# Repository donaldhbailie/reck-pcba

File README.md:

# reck-pcba
The Resourceful Embedded Circuity Kit Printed Circuit Board Assembly (RECK PCBA) is a custom board talored to teach new Peer Instructors (PIs) all of the basic and advanced embedded use cases seen in the HIVE Makerspace.

Integrates a microcontroller, probe-able SPI, I2C, UART, motor drivers, servo drivers, power electronics, and commonly used sensors.

### Basic Embedded:
- ESP32-S3 (Microcontroller Hardware/Software Control Flow)
- Pushbuttons (Digital Input)
- Single LEDs (Digital Output)
- Photoresistor (Analog Input)
- Potentiometer (Analog Input)
- Analog-to-Digital Converter (Internal ADC; Read Analog Signals)
- Magnetic Buzzer (Audio Ouput)
- Voltage Translation (Level Shifting)
  
### Advanced Embedded:
- IMU (SPI Interface)
- Barometric Pressure and Humidity Sensor (SPI Interface)
- IR Ranging Sensor (I2C Interface)
- Digital-to-Analog Converter (I2C Interface; Output Analog Signals)
- Servos (PWM Interface)
- DC Brushed Motors (PWM Interface)
- Chained LEDs (PWM Interface)

## Schematic Preview

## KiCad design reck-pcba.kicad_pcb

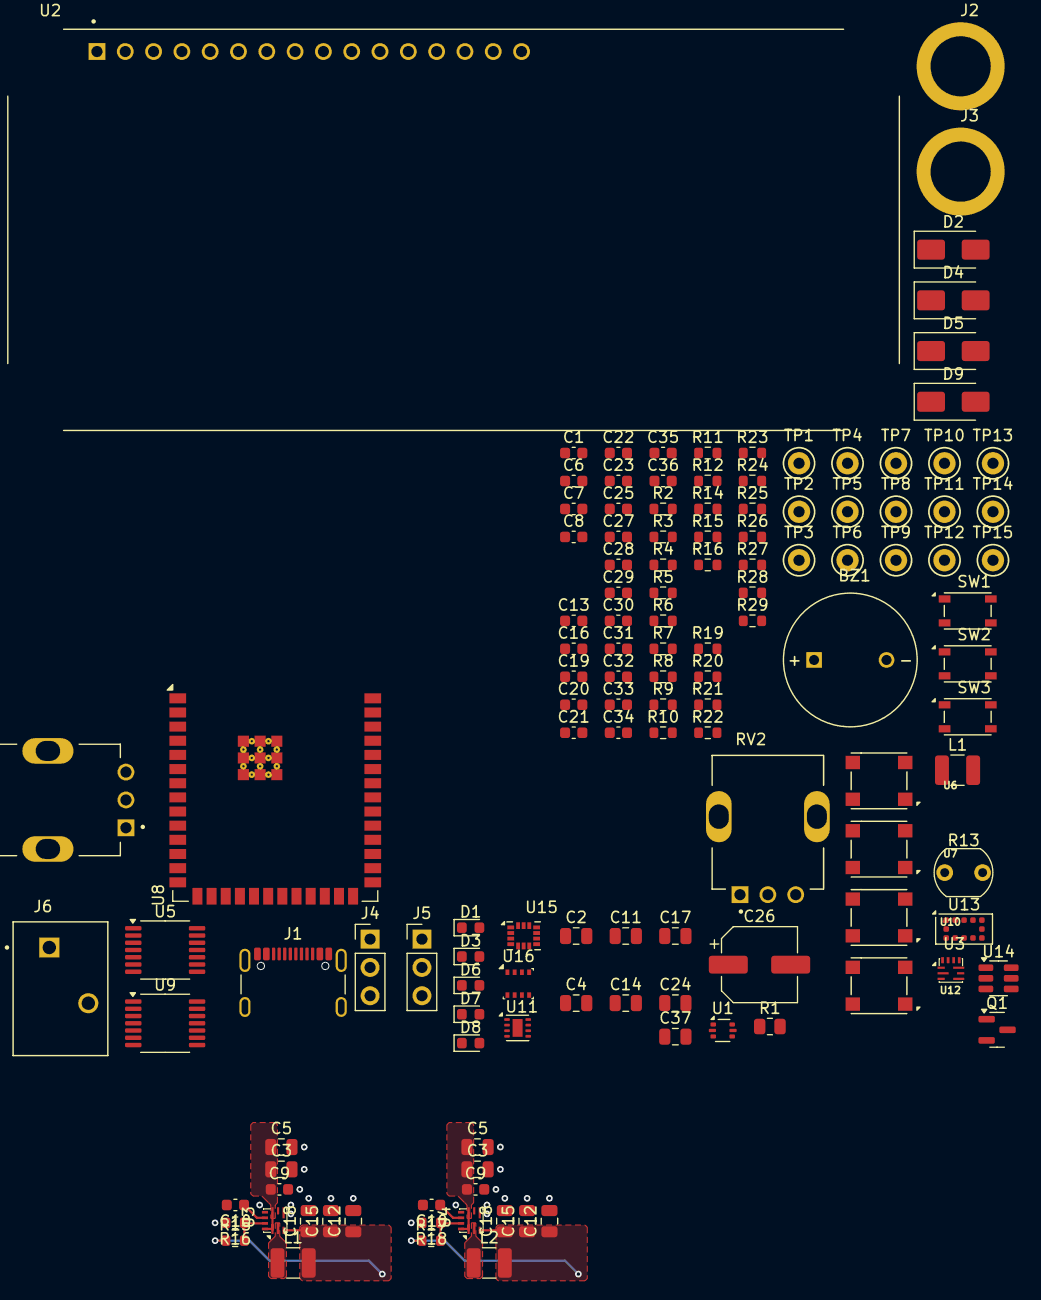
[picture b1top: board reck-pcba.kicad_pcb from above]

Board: 4 copper layers, 132 parts (0 on the bottom side), 75 nets.

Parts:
BZ1: CEM-1206S
C1, C7, C9, C9#2: 2.2nF; C_0603_1608Metric
C2, C3, C3#2, C4, C5, C5#2, C37: 10uF; C_0805_2012Metric
C6, C8, C10, C10#2: 1uF; C_0603_1608Metric
C11, C12, C12#2, C14, C15, C15#2, C17, C18, C18#2, C24: 22uF; C_0805_2012Metric
C13, C16, C19, C20, C21, C22, C23, C25, C27, C28, C29, C30, C31, C32, C33, C34, C35, C36: 100nF; C_0603_1608Metric
C26: 47uF; CP_Elec_6.3x5.9
D1, D3, D6, D7, D8: LED; LED_0603_1608Metric
D2, D4, D9: CDBA340L-HF; D_SMA
D5: 1SMA5928BT3G; D_SMA
J1: USB4105-GF-A; USB_C_Receptacle_GCT_USB4105-xx-A_16P_TopMnt_Horizontal
J2, J3: 575-4
J4, J5: Conn_01x03_Pin; PinHeader_1x03_P2.54mm_Vertical
J6: TBL002A-350-02GR-2OR
L1, L1#2, L2: 2.2uH; L_1210_3225Metric
Q1: BC846; SOT-23
R1: 1M; R_0805_2012Metric
R2, R4, R5, R7, R11, R14, R16, R16#2, R18, R19, R20, R21, R23, R24, R26, R27, R28, R29: 5.1k; R_0603_1608Metric
R3, R25: 1k; R_0603_1608Metric
R6, R8: 330R; R_0603_1608Metric
R9, R10, R12, R22: 130R; R_0603_1608Metric
R13: 02-LDR4; R_LDR_5.1x4.3mm_P3.4mm_Vertical
R15: 16k; R_0603_1608Metric
R15#2, R17: 26.7k; R_0603_1608Metric
RV1, RV2: 10k; PT01-D130D-B103
SW1, SW2, SW3: PTS810_SJM_250_SMTR_LFS
TP1, TP2, TP3, TP4, TP5, TP6, TP7, TP8, TP9, TP10, TP11, TP12, TP13, TP14, TP15: TestPoint; TestPoint_Keystone_5000-5004_Miniature
U1: USBLC6-2P6; SOT-666
U2: LCD2X16
U3, U3#2, U4: TPS62912RPUR; VQFN-HR-10_2x2mm
U5, U9: TXU0104PWR; TSSOP-14_4.4x5mm_P0.65mm
U6, U7, U10, U12: WS2812B
U8: ESP32-S3-WROOM-2
U11: DRV8231ADSGR; WSON-8-1EP_2x2mm_P0.5mm_EP0.9x1.6mm
U13: VL53L0CXV0DH1; ST_VL53L1x
U14: MCP4725A0T-E/CH; SOT-23-6
U15: ISM330DHCXTR; LGA-14_2.5x3.0mm_P0.5mm
U16: BME280; Bosch_LGA-8_2.5x2.5mm_P0.65mm_ClockwisePinNumbering

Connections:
+3V3: BZ1.1, C11.1, C14.1, C17.1, C20.1, C21.1, C23.1, C24.1, C25.1, C27.1, C29.1, C31.1, C32.1, C33.1, C34.1, C35.1, C36.1, C37.1, D7.2 (A), D9.1 (K), L1.2, R2.1, R7.1, R11.1, R13.1, R15.1, R23.1, R24.1, R26.1, R27.1, R28.1, R29.1, RV2.1, U3#2.3 (VO), U5.1 (VCCA), U5.8 (OE), U6.1 (VDD), U7.1 (VDD), U8.2 (3V3), U9.1 (VCCA), U9.8 (OE), U10.1 (VDD), U11.4 (VREF), U12.1 (VDD), U13.1 (AVDDVCSEL), U13.11 (AVDD), U14.3 (VDD), U15.5 (VDD_IO), U15.8 (VDD), U16.6 (VDDIO), U16.8 (VDD)
+5V-EXT: C12.1, C12#2.1, C15.1, C15#2.1, C18.1, C18#2.1, D3.2 (A), J4.1, L1#2.2, L2.2, R15#2.1, R17.1, U3.3 (VO), U4.3 (VO)
+12V-EXT: C3.1, C3#2.1, C5.1, C5#2.1, C9.1, C9#2.1, C26.1, C28.1, D1.2 (A), D4.1 (K), D5.1 (K), U3.1 (EN/SYNC), U3.6 (VIN), U3.10 (S-CONF), U4.1 (EN/SYNC), U4.6 (VIN), U4.10 (S-CONF), U11.5 (VM)
+VBUS: C2.1, C4.1, C7.1, C22.1, C30.1, D2.1 (K), D6.2 (A), R10.1, RV1.1, U1.5 (VBUS), U2.2 (VDD), U3#2.1 (EN/SYNC), U3#2.6 (VIN), U3#2.10 (S-CONF), U5.14 (VCCB), U9.14 (VCCB)
+VBUS-CONN: D2.2 (A), J1.A4 (VBUS), J1.A9 (VBUS), J1.B4 (VBUS), J1.B9 (VBUS)
/ATMO-CS: R28.2, U8.22 (IO14), U16.2 (CSB)
/BOOT-SEL: R7.2, SW2.3, SW2.4, U8.27 (IO0)
/ESP-EN: C6.1, R11.2, SW3.3, SW3.4, U8.3 (EN)
/I2C-SCL: R24.2, TP5.1, U8.18 (IO10), U13.10 (SCL), U14.5 (SCL)
/I2C-SDA: R23.2, TP4.1, U8.17 (IO9), U13.9 (SDA), U14.4 (SDA)
/IMU-CS: R27.2, TP9.1, U8.8 (IO15), U15.12 (CS)
/IMU-INT1: U8.9 (IO16), U15.4 (INT1)
/LCD-DB4: U8.32 (MTCK/IO39), U9.2 (A1)
/LCD-DB4-5V: U2.11 (DB4), U9.13 (B1Y)
/LCD-DB5: U8.33 (MTDO/IO40), U9.3 (A2)
/LCD-DB5-5V: U2.12 (DB5), U9.12 (B2Y)
/LCD-DB6: U8.34 (MTDI/IO41), U9.4 (A3)
/LCD-DB6-5V: U2.13 (DB6), U9.11 (B3Y)
/LCD-DB7: U8.35 (MTMS/IO42), U9.5 (A4)
/LCD-DB7-5V: U2.14 (DB7), U9.10 (B4Y)
/LCD-EN: U5.4 (A3), U8.23 (IO21)
/LCD-EN-5V: U2.6 (E), U5.11 (B3Y)
/LCD-RS: U5.5 (A4), U8.31 (IO38)
/LCD-RS-5V: U2.4 (RS), U5.10 (B4Y)
/LCD-VO: RV1.2, U2.3 (VO)
/MOTOR-IN1: TP2.1, U8.4 (IO4), U11.3 (IN1)
/MOTOR-IN2: TP3.1, U8.5 (IO5), U11.2 (IN2)
/MOTOR-OUT1: J6.1, U11.6 (OUT1)
/MOTOR-OUT2: J6.2, U11.8 (OUT2)
/PWM-BUZZER: R22.1, U8.12 (IO8)
/PWM-LED: U6.4 (DI), U8.7 (IO7)
/PWM-SERVO: TP12.1, U5.3 (A2), U8.6 (IO6)
/PWM-SERVO-5V: J4.2, TP13.1, U5.12 (B2Y)
/SPI-MISO: R26.2, TP8.1, U8.21 (IO13), U15.1 (SDO/SA0), U16.5 (SDO)
/SPI-MOSI: TP6.1, U8.19 (IO11), U15.14 (SDA), U16.3 (SDI)
/SPI-SCLK: TP7.1, U8.20 (IO12), U15.13 (SCL), U16.4 (SCK)
/UART1-RX: J5.2, TP11.1, U8.16 (IO46)
/UART1-TX: J5.1, TP10.1, U8.26 (IO45)
/USB-DN: U1.6 (I/O1), U8.13 (USB_D-/IO19)
/USB-DP: U1.4 (I/O2), U8.14 (USB_D+/IO20)
/USER-BUTTON: R2.2, SW1.3, SW1.4, U8.11 (IO18)
/USER-LED: D8.2 (A), U8.10 (IO17)
/V-DAC: R21.2, TP1.1, U14.1 (VOUT)
/V-DAC-FILT: C13.1, R21.1, U8.15 (IO3)
/V-PHOTO: R13.2, R14.1, R19.2
/V-PHOTO-FILT: C19.1, R19.1, U8.39 (IO1)
/V-POT: R20.2, RV2.2
/V-POT-FILT: C16.1, R20.1, U8.38 (IO2)
GND: C2.2, C3.2, C3#2.2, C4.2, C5.2, C5#2.2, C6.2, C7.2, C8.2, C9.2, C9#2.2, C10.2, C10#2.2, C11.2, C12.2, C12#2.2, C13.2, C14.2, C15.2, C15#2.2, C16.2, C17.2, C18.2, C18#2.2, C19.2, C20.2, C21.2, C22.2, C23.2, C24.2, C25.2, C26.2, C27.2, C28.2, C29.2, C30.2, C31.2, C32.2, C33.2, C34.2, C35.2, C36.2, C37.2, D5.2 (A), J1.A1 (GND), J1.A12 (GND), J1.B1 (GND), J1.B12 (GND), J3.1, J4.3, J5.3, Q1.2 (E), R3.2, R4.2, R5.2, R6.2, R8.2, R9.2, R12.2, R14.2, R16.2, R16#2.2, R18.2, R25.2, RV1.3, RV2.3, SW1.1, SW1.2, SW2.1, SW2.2, SW3.1, SW3.2, TP14.1, TP15.1, U2.1 (VSS), U2.5 (R/W), U2.16 (LEDK), U3.4 (PGND), U3.7 (PSNS), U3#2.4 (PGND), U3#2.7 (PSNS), U4.4 (PGND), U4.7 (PSNS), U5.7 (GND), U6.3 (GND), U7.3 (GND), U8.1 (GND), U8.40 (GND), U8.41 (GND), U9.7 (GND), U10.3 (GND), U11.7 (GND), U11.9 (EP), U12.3 (GND), U13.2 (AVSSVCSEL), U13.3 (GND), U13.4 (GND), U13.6 (GND), U13.12 (GND), U14.2 (VSS), U14.6 (A0), U15.2 (SDX), U15.3 (SCX), U15.6 (GND), U15.7 (GND), U16.1 (GND), U16.7 (GND)
unnamed: D1.1 (K), R3.1
unnamed: D3.1 (K), R6.1
unnamed: D4.2 (A), J2.1
unnamed: D6.1 (K), R8.1
unnamed: D7.1 (K), R9.1
unnamed: D8.1 (K), R12.1
unnamed: BZ1.2, D9.2 (A), Q1.3 (C)
unnamed: J1.A5 (CC1), R5.1
unnamed: J1.B5 (CC2), R4.1
unnamed: J1.A6 (D+), J1.B6 (D+), U1.3 (I/O2)
unnamed: J1.A7 (D-), J1.B7 (D-), U1.1 (I/O1)
unnamed: C1.1, J1.S1 (SHIELD), R1.1
unnamed: Q1.1 (B), R22.2
unnamed: R10.2, U2.15 (LEDA)
unnamed: R15.2, R16.1, U3#2.9 (FB)
unnamed: C8.1, U3#2.8 (NR/SS)
unnamed: L1.1, U3#2.2 (SW)
unnamed: R15#2.2, R16#2.1, R17.2, R18.1, U3.9 (FB), U4.9 (FB)
unnamed: C10.1, C10#2.1, U3.8 (NR/SS), U4.8 (NR/SS)
unnamed: L1#2.1, L2.1, U3.2 (SW), U4.2 (SW)
unnamed: U6.2 (DO), U7.4 (DI)
unnamed: U7.2 (DO), U10.4 (DI)
unnamed: U10.2 (DO), U12.4 (DI)
unnamed: R25.1, U11.1 (IPROPI)
unnamed: R29.2, U13.5 (XSHUT)
SHIELD: C1.2, R1.2, U1.2 (GND)

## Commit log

2024-02-29 Intial Project files
2024-03-06 Added ESP32, Power, LEDs, IMU, and GPS - Added supporting libraries - Added datasheets in the doc/datasheet folder
2024-03-15 Added new uC, Power, and Motor support - Updated ESP32-C3 to ESP32-S3 due to GPIO constraints - Using two buck regulators for servo 5V power and board 3V3
2024-03-27 Full Schematics Complete - Changed uC to ESP32-S3-WROOM-2 to allow for pinout discussion. - Moved buck regulators to main sheet. - Added titles and descriptions to each Sensor, Interface, or concept.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
2024-03-27 Updated IR TOF Sensor Wording - Changed "IR LASER TOF SENSOR" to "IR TIME-OF-FLIGHT (TOF) SENSOR". - Updated Schematic. - Updated PDF.
2024-03-27 Update README.md
    - Added Schematic Preview.
